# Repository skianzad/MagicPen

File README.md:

ReadMe

***************************************************************
Installing Bno055
When using a serial UART device with the Raspberry Pi you'll need to make sure you disable the kernel's use of the Pi's serial port.  Normally when the Pi kernel boots up it will put a login terminal on the serial port, however if you connect a device like the BNO055 to this serial port it will get confused by the login terminal.  Luckily it's easy to disable the kernel's use of the serial port by using the raspi-config tool.
To disable the kernel serial port connect to the Raspberry Pi in a terminal (using SSH) and launch the raspi-config tool by running:
$ sudo raspi-config
Navigate the menus to the interfacomg options-> P6  Serial option and when prompted if you want a login shell over the serial port select No.  Then select the Finish menu option to exit raspi-config.
To install the software for this project you'll need to make sure your Raspberry Pi is running the latest Raspbian operating system, or your BeagleBone Black is running the latest Debian operating system.  Make sure your board is connected to the internet through a wireless or wired network connection too.

Connect to your board in a command line terminal and run the following commands to install the necessary dependencies:

sudo apt-get install -y build-essential python-dev python-smbus python-pip git

***************************************************************
Installing pyqt4 
$ sudo apt-get update
$ sudo apt-get install qt4-default

***No need***
$ sudo apt-get install qt5-default pyqt5-dev pyqt5-dev-tools
If the system is not working at this level then do the following
QT Core needs to be installed with
$ sudo apt-get install qt5-default
You'll need to copy over sip and PyQt5 to your Raspberry Pi (I used SFTP). Just put the tar files someplace that you can get to them easily.
You'll need to extract each of them, using the tar command, with the -xzvf tag so you'll end up with tar -xzvf sip-4.19.1.tar.gz`for sip.
In each folder, you'll need to set up for the build. This is done by typing "python config.py" in each directory.
The contents of each directory needs to be built and installed, go to your sip folder and type "make" this will take a very long time. After it's through, type "sudo make install".
Now do the same thing in your PyQt5 directory.

****************************************************************************
Installing Bluepy

sudo apt-get install libgtk2.0-dev

sudo pip install bluepy
sudo python3 -m pip install bluepy

**********************To motors********************************
PWM1	= 	GPIO 18 (pin 12) 
PWM2	=	GPIO 13  (pin33) 
DIR1      =	GPIO  20
DIR2      =	GPIO  16
********************To the trackball********************************
UP 	=	GPIO  22 
DOWN	=	GPIO  23
LEFT	=	GPIO 27
RIGHT	= 	GPIO 17
BUTTON=	GPIO 24
VCC
Gnd

*******************To the orientation sensor********************************
SPI1 	=	GPIO  10
SPI2	=	GPIO  9
SPI3	= 	GPIO 11
VCC	=	3.3V (you do not need to connect it to 5Vs)
Gnd

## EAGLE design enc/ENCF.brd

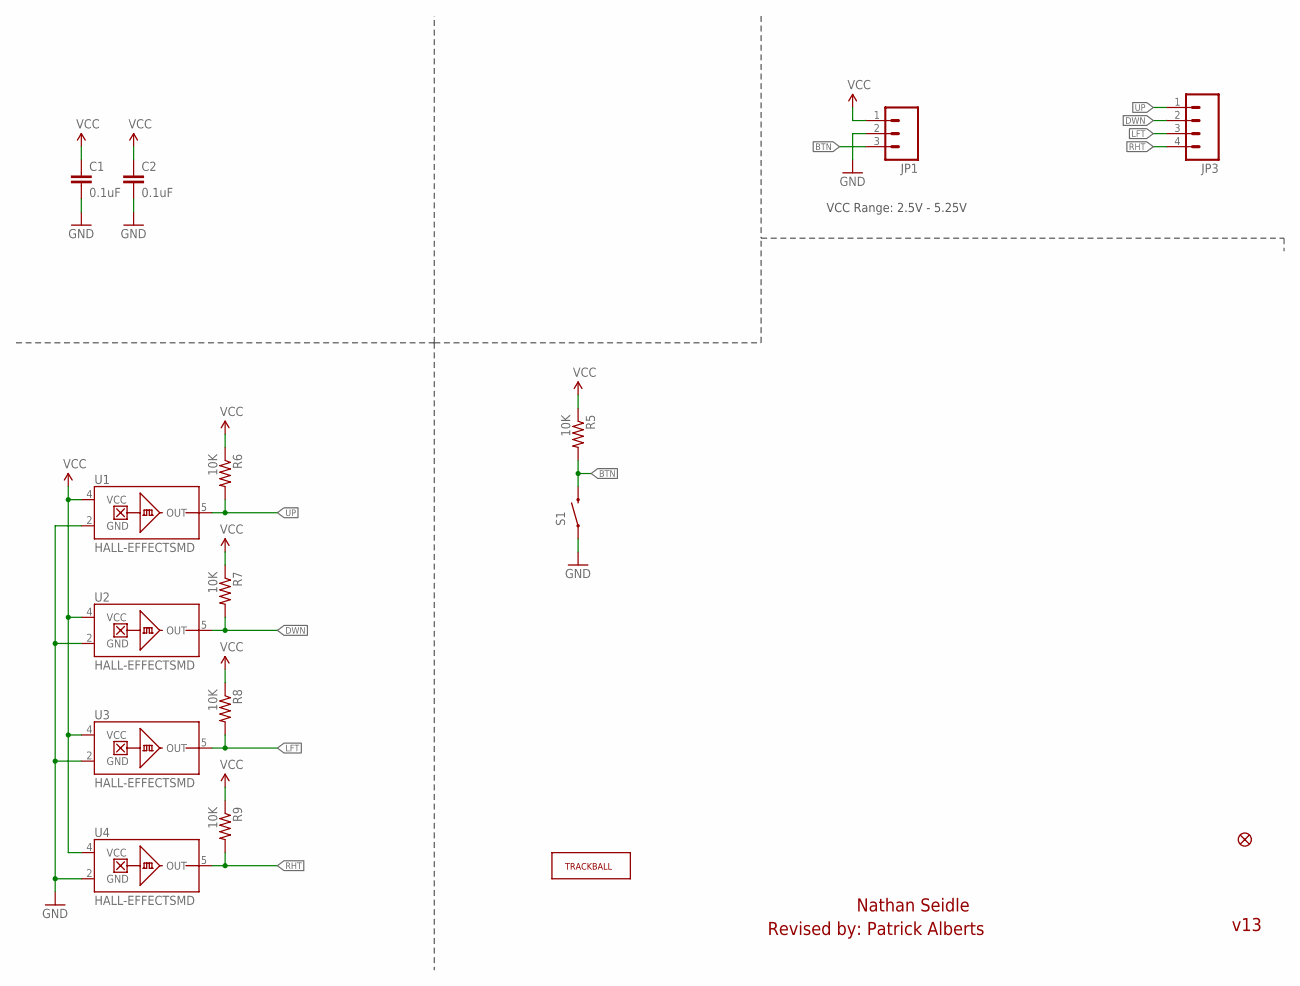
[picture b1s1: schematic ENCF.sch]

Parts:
C1, C2: 0.1uF; 0603-CAP
E$2: FIDUCIAL1X2; FIDUCIAL-1X2
JP1: M03PTH; 1X03
JP3: M04PTH; 1X04
R5, R6, R7, R8, R9: 10K; 0603-RES
S1: SWITCH-MOMENTARY-2SMD-2; TACTILE_SWITCH_SMD-2
U1, U2, U3, U4: HALL-EFFECTSMD; SC70
U$3: TRACKBALLMECH; TRACKBALL

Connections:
BTN: JP1.3, R5.2, S1.1 (2)
DWN: JP3.2, R7.2, U2.5 (OUT)
GND: C1.2, C2.2, JP1.2, S1.2 (1), U1.2 (GND), U2.2 (GND), U3.2 (GND), U4.2 (GND)
LFT: JP3.3, R8.2, U3.5 (OUT)
RHT: JP3.4, R9.2, U4.5 (OUT)
UP: JP3.1, R6.2, U1.5 (OUT)
VCC: C1.1, C2.1, JP1.1, R5.1, R6.1, R7.1, R8.1, R9.1, U1.4 (VCC), U2.4 (VCC), U3.4 (VCC), U4.4 (VCC)

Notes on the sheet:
v13
Nathan Seidle
Revised by: Patrick Alberts
VCC Range: 2.5V - 5.25V

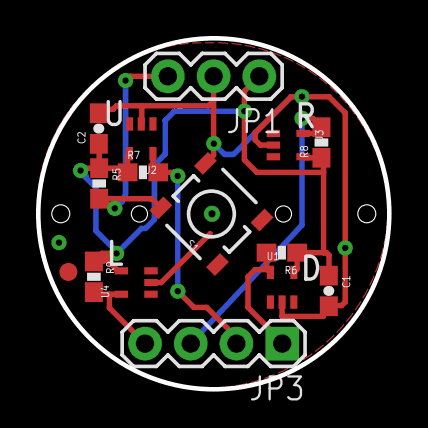
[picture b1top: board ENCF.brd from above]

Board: 2 copper layers, 19.5 x 19.5 mm, 16 parts (0 on the bottom side), 7 nets.

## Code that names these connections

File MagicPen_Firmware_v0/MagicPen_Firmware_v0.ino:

/**
 ************************************************************************************************
 * @file       Haply_Arduino_Control.ino
 * @author     Steve Ding, Colin Gallacher
 * @version    V0.1.0
 * @date       27-February-2017
 * @brief      Haply board control for encoder read and torque write using on-board actuator
 *             ports
 ************************************************************************************************
 * @attention
 *
 *
 ************************************************************************************************
 */

/* includes ************************************************************************************/
#include <stdlib.h>
#include <Encoder.h>
#include <pwm01.h>
#include "Haply_Arduino_Control.h"



/* Actuator parameter declarations *************************************************************/
actuator 	Motor1;
actuator 	Motor2;
actuator 	Motor3;
actuator 	Motor4;


/* Actuator Status and Command declarations ****************************************************/

/* Address of device that sent data */
byte 		device_address;

/* communication interface control, defines type of instructions recieved */
byte 		cmd_code;  

/* Active actuators indicator */
byte 		motors_active[TOTAL_ACTUATORS]; 

/* Number of motors actively setup and used */
int  		number_of_motors;  

/* communication interface control, defines response to send */
byte 		reply_code = 3;


/* Iterator and debug definitions **************************************************************/
long 		lastPublish = 0;
int  		ledPin = 13;



/* main setup and loop block  *****************************************************************/

/**
 * @brief    Main setup function, defines parameters and hardware setup
 */
void setup() {
	pinMode(ledPin, OUTPUT);
	digitalWrite(ledPin, LOW);
	SerialUSB.begin(115200);
 pinMode(Lft, INPUT_PULLUP);
attachInterrupt(digitalPinToInterrupt(Lft), Right, CHANGE);
pinMode(Rht,INPUT_PULLUP);
attachInterrupt(digitalPinToInterrupt(Rht), Left, CHANGE);
pinMode(Up, INPUT_PULLUP);
attachInterrupt(digitalPinToInterrupt(Up), Upa, CHANGE);
pinMode(Dwn, INPUT_PULLUP);
attachInterrupt(digitalPinToInterrupt(Dwn), Down, CHANGE);
}


/**
 * @brief    Main loop function
 */
void loop() {
  
	if(micros() - lastPublish >= 50){
    
		lastPublish = micros();

		if(SerialUSB.available() > 0){
      
			cmd_code = command_instructions(SerialUSB.read(), &number_of_motors, motors_active);
			
			switch(cmd_code){
				case 0:
					device_address = setup_actuators(&Motor1, &Motor2, &Motor3, &Motor4, number_of_motors, motors_active);
					reply_code = 0;
					break;
				case 1:
					device_address = write_torques(&Motor1, &Motor2, &Motor3, &Motor4, number_of_motors, motors_active);
					reply_code = 1;
					break;
				default:
					break; 
			}
		}
		else{

			switch(reply_code){
				case 0:
					reply_code = 3;
					break;
				case 1:
					read_encoders(&Motor1, &Motor2, &Motor3, &Motor4, number_of_motors, device_address, motors_active);
					reply_code = 3;
					break;
				default:
					break; 
			} 
		}
	}
}

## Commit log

2017-07-03 Adding buttons end edditing sliders
2017-07-03 removing test codes
2017-07-03 Developing the server version
2017-10-24 Adding working version of graphvis
2017-10-24 Fixing the Kinematics of folowing a path
2018-02-17 Create FeelGraph
2018-02-17 Rename e4_more_gestures.pde to 1Dstroke.pde
2018-02-17 add Util java library
2018-02-17 training added
2018-02-17 Sending back the discovered template
2018-02-17 drawing is added
2018-02-18 Adding Fisica library
2018-02-19 Spring added
2018-02-20 Removing the short draggs
2018-02-21 adding spring image and joint connection
2018-02-21 some bugs got fixed
2018-02-22 Mass No rotation
2018-02-22 spring Joint added
2018-02-22 bugs fixed
2018-02-22 Spring parallel and series added
2018-02-22 spring index
2018-02-23 adding drawing part
2018-03-01 Adding haptic feedback
2018-03-15 Change some parameters
2018-03-23 update before demo1
2018-03-23 update before demo2
2018-03-24 update before demo3
2018-03-24 road problem solved
2018-05-23 test
2018-05-24 recovery done
2018-05-24 no changes
2018-05-24 fixed the charge offset problem
2018-05-25 added torque graphs in main (electric charges)
2018-05-25 added smartpen sample app file
2018-05-29 main: torque graphs dependent on size of screen. electric_rec: attached FBodies to each charge (to enable dragging).
2018-06-03 Adding the graph example on Proccessing
2018-06-04 Adding the PCB data
2018-06-04 different graphs added
2018-06-04 added sample app with smartpen SDK. fixed car race.
2018-06-05 Feeling a graph guiding part added
2018-06-05 added custom function graph1
2018-06-07 added text boxes and UI
2018-06-14 fixed some bugs in main.pde
2018-06-14 deleted extra main file
2018-06-14 fixed torque graphics
2018-07-03 added graph_merge (latest v. so far)
2018-07-17 added position-based drive option
2018-07-18 added drawing_graph (position-track guidance)
2018-07-25 changed drawing_graph's algorithm to be tangent-driven
2018-08-05 Added modified code for wifi communication with ArduinoDUE using esp8266
2018-12-06 Lena's Last updates
2018-12-07 Last merge
2018-12-07 sample app added
2019-01-22 A CAD tool prototype written in Python
2019-02-09 Restructured the CAD code, fixed the drawing connection problem
2019-02-13 Increased drawing display resolution and implemented virtual button functionality
2019-02-25 Added a PyQt4 version of the program. Added drawing Bezier curve function
2019-02-26 Added WiFi functions to communicate with RPi server
2019-03-01 added bluetooth connection
2020-01-30 initial commit of powerpen files
2020-02-05 added memory feature, not tested if compiles or not
2020-02-05 Feb5
2020-02-05 tested circle relation code. Need to add hover mode and other relations
2020-02-07 merged memory feature with Yuxiang's relation feature
2020-02-07 ignore VS Code config directory
2020-02-12 classes for various shapes
2020-02-12 added repositioning feature; also replaced shape dicts with shape classes
2020-02-15 basic distance constraint implemented
2020-02-15 polished virtual ruler functionality
2020-04-29 modified alignment based on new specs; added delta display
2020-04-29 aux line done
2020-05-04 set max separation for alignment to 10
2020-05-04 allows reconnect to pen after auto power-off
2020-05-11 added concentric relation
2020-05-11 changed ruler's offset; added delta & auxiliary line support for distance and concentric relation
2020-05-14 added parallel & perpendicular relation
2020-05-20 added aux arc for parallel & perpendicular; for those relations fixed bugs with rotations
2020-06-18 extended relations to arcs
2020-06-18 fixed applying same constraint multiple times after pen lifted
2020-06-18 fixed bug with auxiliary arc across 1st and 4th quadrant; simplified paintArc's span angle calcuation
2020-06-18 draw auxiliary lines for arcs on which relations are applied
2020-07-10 Enabling the hover mode
2020-07-15 adding the BLtest
2020-07-21 added delta displays while hovering for circle, rectangle, line and arc drawing
2020-07-28 removed relations as class objects
2020-07-29 substituted prints with loggings
2020-08-03 allows setting logging level for each module
2020-08-17 steering law boundary check for circles, rectangles, lines
2021-03-20 Added WiFi module to communicate with Processing
2021-03-21 send pen data once per stroke; let the client interpolate points
2021-03-21 fixed server address to bind with socket
2021-06-15 python3 upgrade
2021-06-15 working
2021-06-16 python3!
2021-06-16 added udp server
2021-06-16 a bit of cleanup
2021-06-17 started on api
2021-06-21 some changes
2021-06-23 trying to reduce bt latency
2021-07-07 added Go api
2021-07-07 updated Go API
2021-07-13 added go module files

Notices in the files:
parts and their libraries:
SparkFun-Capacitors: Licensing: Creative Commons ShareAlike 4.0 International - https://creativecommons.org/licenses/by-sa/4.0
